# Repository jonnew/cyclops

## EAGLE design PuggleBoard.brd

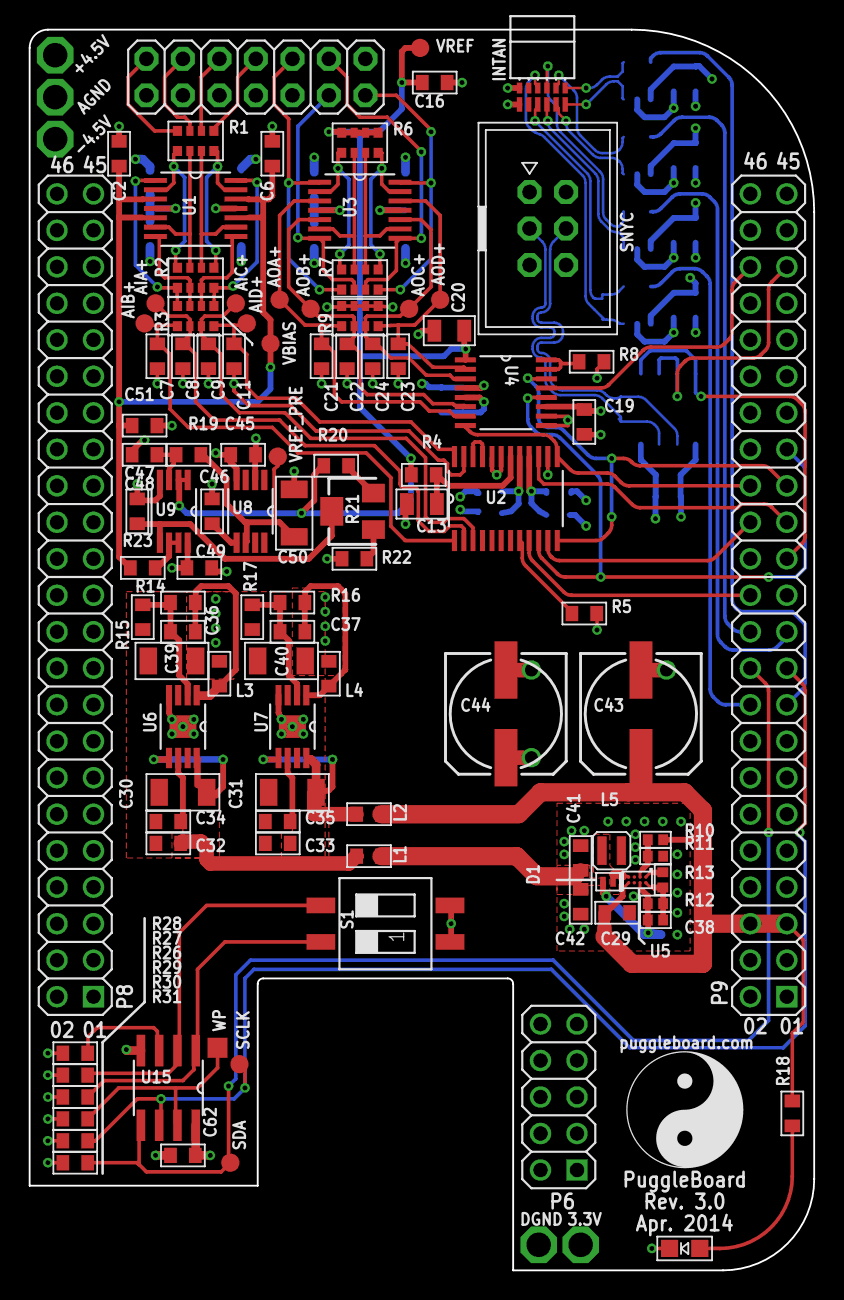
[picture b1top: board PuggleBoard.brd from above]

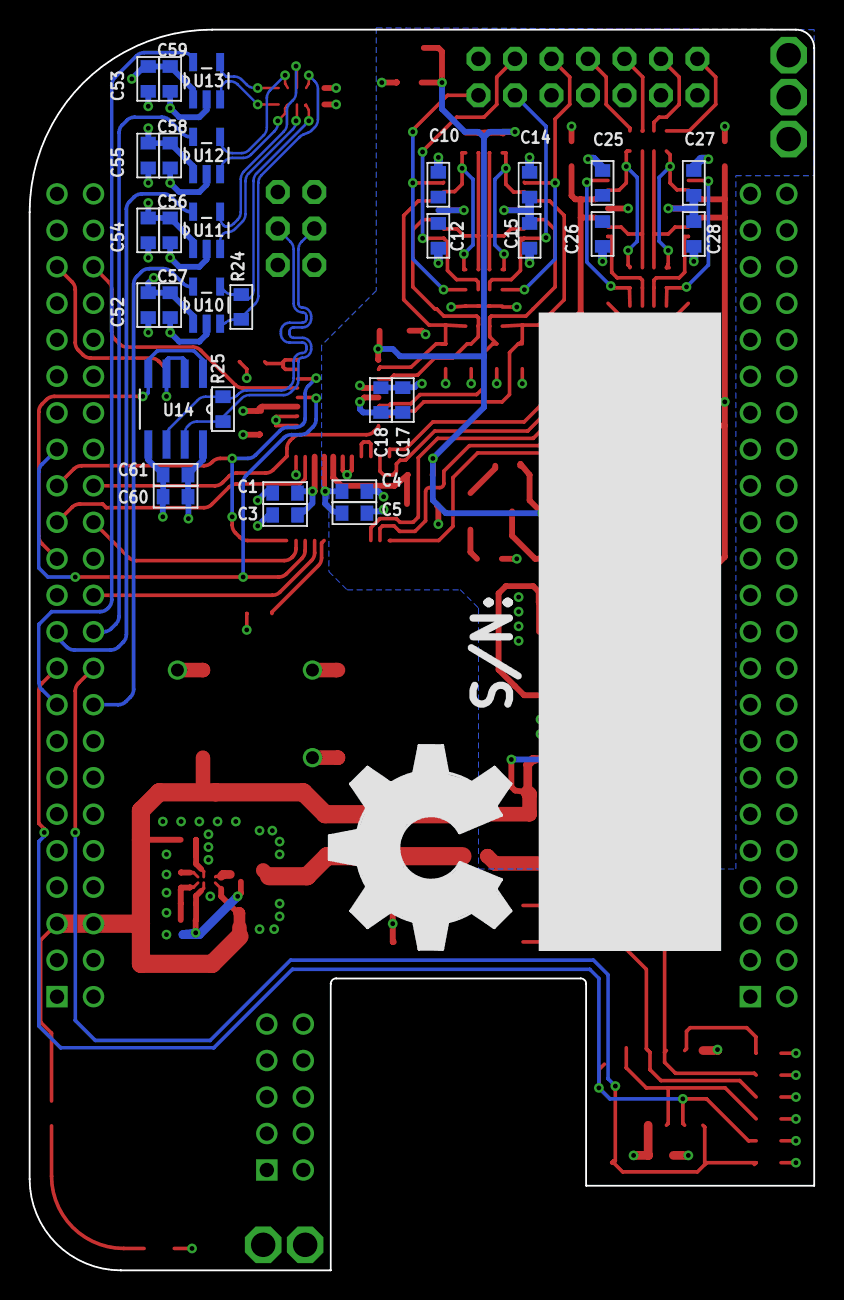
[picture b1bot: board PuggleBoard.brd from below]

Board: 4 copper layers, 54.6 x 86.4 mm, 141 parts (32 on the bottom side), 89 nets.

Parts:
3.3V: TPPAD1-17; P1-17
+4.5V: TPPAD1-17; P1-17
-4.5V: TPPAD1-17; P1-17
AGND: TPPAD1-17; P1-17
AIA+: TPB1,27; B1,27
AIB+: TPB1,27; B1,27
AIC+: TPB1,27; B1,27
AID+: TPB1,27; B1,27
AOA+: TPB1,27; B1,27
AOB+: TPB1,27; B1,27
AOC+: TPB1,27; B1,27
AOD+: TPB1,27; B1,27
A_I/O: PINHD-2X7; 2X07
BB1: BEAGLEBONE_OUTLINEPUGGLEBOARD; PUGGLEBOARD_SHIELD
C1, C4, C17: 4.7uF; 0603
C2, C3, C5, C6, C12, C15, C16, C18, C19, C26, C28, C47, C48, C49, C51, C52, C53, C54, C55, C60, C62: 0.1uF; 0603
C7, C8, C9, C11: 68nF; 0603
C10, C14, C25, C27, C45, C46: 1uF; 0603
C13: 22uF; 0805
C20: 10uF; 0805
C21, C22, C23, C24: 0603
C29: 10uF; 0603
C30, C31, C39, C40: 10uF; 1206
C32, C33, C56, C57, C58, C59, C61: 1nF; 0603
C34, C35, C36, C37: 10nF; 0603
C38: 10pF; 0402
C41, C42: 22uF; 0603
C43, C44: 47uF; 153CLV-0807
C50: 4.7uF; 1206
D1: PMEG3005EL; SOD882
DGND: TPPAD1-17; P1-17
INTAN: RHD2000-CABLE-DAQ-SIDE; OMNETICS_PZN-12-AA
L1, L2, L3, L4: MPZ1608; 0603
L5: 6.8uH; VLS2012E
PWR: LEDGREEN_0805; CHIP-LED0805
R1, R6, R7: 2k; RX4_0612
R2: 1k; RX4_0612
R3: 100; RX4_0612
R4: 10; 0603
R5, R8, R19, R23, R29: 10k; 0603
R9: RX4_0612
R10, R11: 20k; 0402
R12: 180k; 0402
R13: 39k; 0402
R14, R16: 13.7k; 0603
R15, R17, R26, R27, R28: 4.7k; 0603
R18: 1k; 0603
R20, R30, R31: 5.6k; 0603
R21: 2k; SM-42/43W
R22: 2k; 0603
R24: 100; 0603
R25: 150; 0603
S1: ADDRESS; SMS-002
SCLK: TPB1,27; B1,27
SDA: TPB1,27; B1,27
SNYC: PINHD-2X3_IDC; 2X03_IDC
U1: LMP7704; SOP65P640X120-14N-MOD
U2: ADS8331; SOP65P640X120-24N
U3: OPA4209; SOP65P640X120-14N-MOD
U4: AD5686; MO-153-AB
U5: LMR70503; 8BGA
U6: 3001; SOP65P490X110-9N
U7: 4901; SOP65P490X110-9N
U8: 5040; SOP65P490X110-8N
U9: 8032; SOP65P490X110-8N
U10: SN65LVDS2; SOT95P280X145-5N
U11, U12, U13: SN65LVDS1; SOT95P280X145-5N
U14: SN65MLVD201; SOIC127P600X175-8N
U15: 24C; SO-08
U$1: PB-LOGO-NOSITE
U$2: OSHW_FILLX500_NOTEXT
VBIAS: TPB1,27; B1,27
VREF: TPB1,27; B1,27
VREF_PRE: TPB1,27; B1,27
WP: TPTP14SQ; TP14SQ

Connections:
+4.5V: +4.5V.TP, C4.2, C5.2, C14.1, C15.1, C17.1, C18.1, C27.1, C28.1, C40.1, C45.2, C49.1, L4.2, U1.4, U2.17, U3.4, U4.5, U8.2, U9.8
+4.5V_PRE: C37.1, L4.1, R16.1, U7.1
-4.5V: -4.5V.TP, C10.1, C12.1, C25.1, C26.1, C39.1, L3.2, U1.11, U3.11
-4.5V_PRE: C36.1, L3.1, R14.1, U6.1
ADC_-IN_A: R1.P1, R2.P2, U1.2
ADC_-IN_B: R1.P3, R2.P4, U1.6
ADC_-IN_C: R1.P5, R2.P6, U1.9
ADC_-IN_D: R1.P7, R2.P8, U1.13
ADC_A: A_I/O.2, R1.P2
ADC_A+: R2.P1, R3.P2, U1.1
ADC_B: A_I/O.4, R1.P4
ADC_B+: R2.P3, R3.P4, U1.7
ADC_C: A_I/O.6, R1.P6
ADC_C+: R2.P5, R3.P6, U1.8
ADC_D: A_I/O.8, R1.P8
ADC_D+: R2.P7, R3.P8, U1.14
AGND1: C37.2, R16.2, R17.1, U7.2
AGND2: C36.2, R14.2, R15.1, U6.2
CS1_N: INTAN.T1, U13.3
CS1_P: INTAN.B1, U13.4
DAC_+IN_A: AOA+.TP, C21.1, R9.P8, U3.3, U4.7
DAC_+IN_B: AOB+.TP, C22.1, R9.P6, U3.5, U4.6
DAC_+IN_C: AOC+.TP, C24.1, R9.P4, U3.10, U4.3
DAC_+IN_D: AOD+.TP, C23.1, R9.P2, U3.12, U4.2
DAC_-IN_A: R6.P1, R7.P2, U3.2
DAC_-IN_B: R6.P3, R7.P4, U3.6
DAC_-IN_C: R6.P5, R7.P6, U3.9
DAC_-IN_D: R6.P7, R7.P8, U3.13
DAC_A: A_I/O.10, R7.P1, U3.1
DAC_B: A_I/O.11, R7.P3, U3.7
DAC_C: A_I/O.12, R7.P5, U3.8
DAC_D: A_I/O.13, R7.P7, U3.14
GND: AGND.TP, A_I/O.1, A_I/O.3, A_I/O.5, A_I/O.7, A_I/O.9, A_I/O.14, BB1.1, BB1.2, BB1.47, BB1.48, BB1.89, BB1.90, BB1.91, BB1.92, C1.2, C2.2, C3.2, C4.1, C5.1, C6.2, C7.1, C8.1, C9.1, C10.2, C11.1, C12.2, C13.1, C14.2, C15.2, C16.2, C17.2, C18.2, C19.2, C20.2, C21.2, C22.2, C23.2, C24.2, C25.2, C26.2, C27.2, C28.2, C29.2, C30.2, C31.2, C32.2, C33.2, C34.2, C35.2, C39.2, C40.2, C41.1, C42.1, C43.-, C44.-, C45.1, C46.1, C47.2, C48.2, C49.2, C50.2, C51.2, C52.2, C53.2, C54.2, C55.2, C56.2, C57.2, C58.2, C59.2, C60.2, C61.2, C62.2, DGND.TP, INTAN.T6, L5.2, PWR.C, R9.P1, R9.P3, R9.P5, R9.P7, R11.2, R15.2, R17.2, R22.2, S1.1, S1.2, SNYC.1, SNYC.2, SNYC.5, SNYC.6, U2.14, U2.19, U2.20, U2.23, U4.4, U4.9, U4.10, U5.C1, U5.C2, U6.4, U6.9, U7.4, U7.9, U8.4, U9.4, U10.2, U11.2, U12.2, U13.2, U14.5, U15.4
I2C2_SCL: BB1.65, R30.1, SCLK.TP, U15.6
I2C2_SDA: BB1.66, R31.1, SDA.TP, U15.5
MASTER/SLAVE: BB1.87, U14.2, U14.3
MISO1_N: INTAN.T4, R24.2, U10.4
MISO1_P: INTAN.B4, R24.1, U10.3
MOSI_N: INTAN.T3, U11.3
MOSI_P: INTAN.B3, U11.4
unnamed: C35.1, U7.6
unnamed: C34.1, U6.6
unnamed: U2.21, U2.22
unnamed: C48.1, R21.2, U9.5
unnamed: R10.2, R11.1, U5.B1
unnamed: R21.1, R22.1
unnamed: R23.2, U9.6, U9.7
unnamed: R20.2, R21.3
unnamed: R26.1, S1.4, U15.1
unnamed: C13.2, R4.1, U2.18
unnamed: C38.2, R12.2, R13.1, U5.A2
unnamed: R27.1, S1.3, U15.2
unnamed: R28.1, U15.3
unnamed: PWR.A, R18.1
unnamed: R29.1, U15.7, WP.TP
unnamed: R13.2, U5.A1
unnamed: C47.1, R19.1, U9.3
unnamed: C46.2, U8.5
unnamed: AIA+.TP, C7.2, R3.P1, U2.1
unnamed: AIB+.TP, C8.2, R3.P3, U2.2
unnamed: AIC+.TP, C9.2, R3.P5, U2.3
unnamed: AID+.TP, C11.2, R3.P7, U2.24
SCLK_N: INTAN.T2, U12.3
SCLK_P: INTAN.B2, U12.4
SPI0: BB1.74, U2.11
SPI1: BB1.88, U4.13
SPI2: BB1.77, U2.10, U4.12
SPI3: BB1.75, U2.12, U4.14
SPI4: BB1.76, U2.13, U4.8
SPI5: BB1.73, U2.15
SPI6: BB1.70, U2.9
SPI7: BB1.63, U13.5
SPI8: BB1.68, U12.5
SPI9: BB1.67, U11.5
SPI10: BB1.64, U10.5
SW: D1.C, L5.1, U5.D1
SYNC: BB1.71, U14.1, U14.4
SYNC_N: R25.2, SNYC.3, U14.7
SYNC_P: R25.1, SNYC.4, U14.6
VBIAS: C2.1, C6.1, C51.1, R23.1, U1.3, U1.5, U1.10, U1.12, VBIAS.TP
VDD_5V: BB1.51, BB1.52, C29.1, C43.+, L2.1, R10.1, R18.2, U5.D2
VDD_POST_LC: C31.1, C33.1, L2.2, U7.5, U7.8
VDRIVE: 3.3V.TP, BB1.49, BB1.50, C1.1, C3.1, C19.1, C44.+, C52.1, C53.1, C54.1, C55.1, C56.1, C57.1, C58.1, C59.1, C60.1, C61.1, C62.1, INTAN.B6, R5.2, R8.2, R26.2, R27.2, R28.2, R29.2, R30.2, R31.2, U2.16, U4.11, U10.1, U11.1, U12.1, U13.1, U14.8, U15.8
VOUT-: C38.1, C41.2, C42.2, D1.A, L1.1, R12.1, U5.B2
VREF: C16.1, C20.1, R4.2, R6.P2, R6.P4, R6.P6, R6.P8, R20.1, U4.1, U9.1, U9.2, VREF.TP
VREF_PRE: C50.1, R19.2, U8.6, VREF_PRE.TP
VSS_POST_LC: C30.1, C32.1, L1.2, U6.5, U6.8
~ADCRST: R5.1, U2.8
~DACRST: R8.1, U4.15, U4.16

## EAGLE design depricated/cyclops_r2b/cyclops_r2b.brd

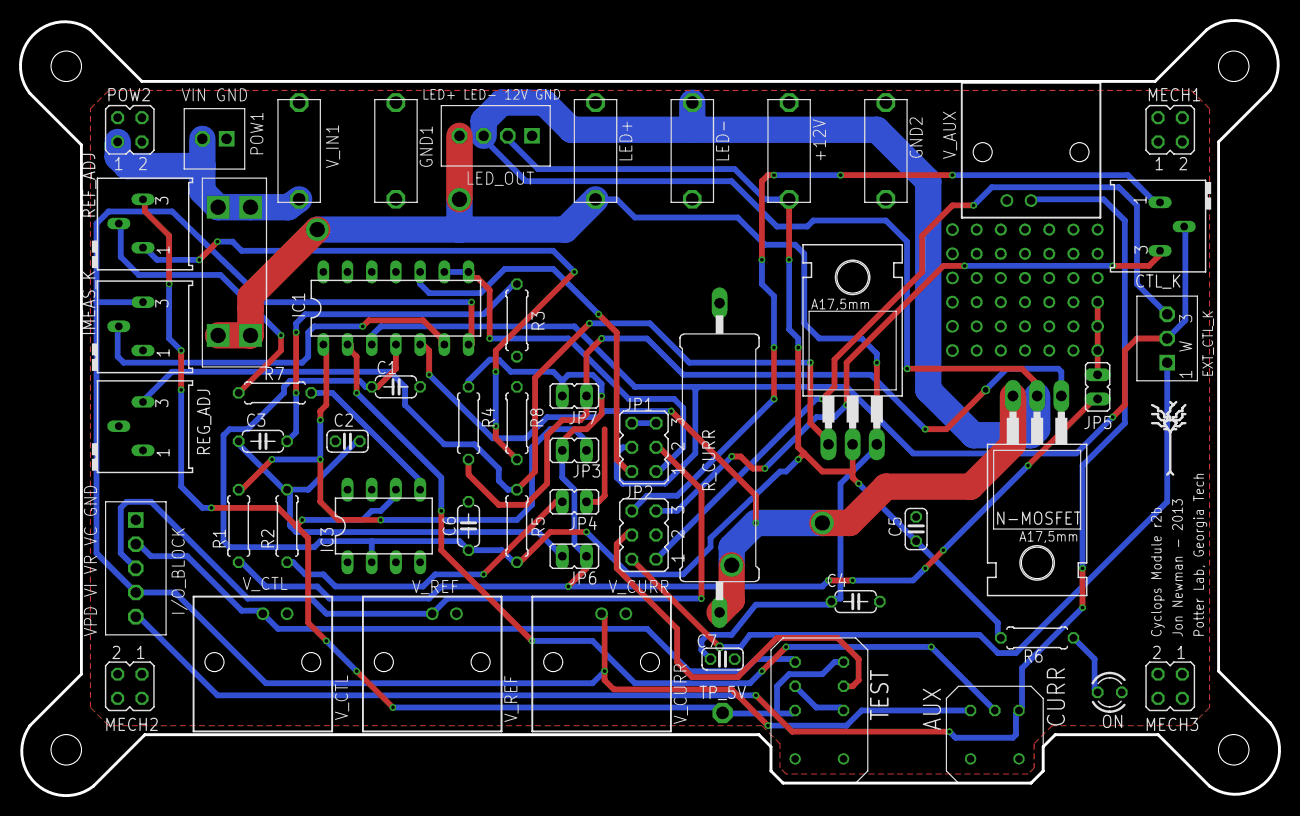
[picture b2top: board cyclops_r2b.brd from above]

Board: 2 copper layers, 132.2 x 81.4 mm, 55 parts (1 on the bottom side), 34 nets.

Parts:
+12V: BANANA_TO_BOARD
C1, C3, C4, C6: 0.1uF; C050-024X044
C2, C5: 1.0uF; C025-024X044
C7: 10uF; C025-024X044
CTL_K: 10k; RJ6S
CURR/OPT: A_TOGGLE_SPST
EXT_CTL_K: SCREW3
GND1, GND2: BANANA_TO_BOARD
I/O_BLOCK: SCREW5
IC1: LM324N; DIL14
IC2: 317; TO220BH
IC3: REF02; DIL08-OVAL
IMEAS_K: 10k; RJ6S
JP1, JP2: JP3Q
JP3, JP4, JP5, JP6, JP7: JP1
LED+: BANANA_TO_BOARD
LED-: BANANA_TO_BOARD
LED_OUT: SCREW4
MECH1, MECH2, MECH3: JP2Q
N-MOSFET: TO220BH
ON: LED3MM
POW1: SCREW2
POW2: JP2Q
R1, R2, R4: 0R; 0207/7
R3: 120; 0207/7
R5: 240; 0207/7
R6: 1.5k; 0207/7
R7: 470; 0207/7
R8: 1k; 0207/7
REF_ADJ: 10k; RJ6S
REG_ADJ: 5k; RJ6S
R_CURR: 0.2; IMEAS_R
TEST: 320-938
TP_5V: P1-13
U$1: FUSE >2A; NXT-FUSE
U$2: OSHW_FILLX750_NOTEXT
V_AUX: 1-227161-0; AMP_227161
V_CTL: 1-227161-0; AMP_227161
V_CURR: 1-227161-0; AMP_227161
V_IN1: BANANA_TO_BOARD
V_REF: 1-227161-0; AMP_227161

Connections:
GND: C1.2, C2.2, C4.2, C5.2, C6.2, C7.1, GND1.P$1, GND1.P$2, GND2.P$1, GND2.P$2, I/O_BLOCK.P$1, IC1.11, IC3.4, IMEAS_K.A, JP2.3, JP4.1, LED_OUT.P$1, ON.K, POW1.P$1, POW2.4, R3.1, R8.2, REG_ADJ.S, R_CURR.1, V_AUX.2, V_CTL.2, V_CURR.2, V_REF.2
unnamed: CURR/OPT.P$2, IC1.2
unnamed: IC1.5, N-MOSFET.S, R_CURR.2
unnamed: IC1.1, JP3.2, R1.2
unnamed: CURR/OPT.P$1, I/O_BLOCK.P$4, IC1.7, IMEAS_K.E, V_CURR.1
unnamed: CURR/OPT.P$3, I/O_BLOCK.P$5, V_AUX.1
unnamed: JP2.4, TEST.P$2
unnamed: CTL_K.E, JP2.5
unnamed: CTL_K.S, EXT_CTL_K.P$2, IC1.3, JP1.4
unnamed: IC1.8, IC1.9, JP1.1
unnamed: I/O_BLOCK.P$2, TEST.P$4, V_CTL.1
unnamed: C2.1, C3.1, JP6.2, R2.2
unnamed: CTL_K.A, JP2.6
unnamed: C3.2, R3.2
unnamed: IC1.10, JP1.2
unnamed: IC1.6, IMEAS_K.S
unnamed: JP1.5, JP1.6
unnamed: I/O_BLOCK.P$3, JP1.3, V_REF.1
unnamed: IC2.G, R5.1, REG_ADJ.E
unnamed: IC3.5, R7.2
unnamed: LED-.P$1, LED-.P$2, LED_OUT.P$3, N-MOSFET.D
unnamed: R7.1, REF_ADJ.S
unnamed: TEST.P$3, TEST.P$5
unnamed: R8.1, REF_ADJ.A
unnamed: EXT_CTL_K.P$1, JP2.2
unnamed: EXT_CTL_K.P$3, JP2.1
unnamed: JP4.2, R2.1
unnamed: ON.A, R6.1
unnamed: JP3.1, JP5.2, JP6.1, JP7.2, R1.1, R4.2
unnamed: JP7.1, N-MOSFET.G, R4.1
P_12V: +12V.P$1, +12V.P$2, C1.1, C5.1, C6.1, IC1.4, IC2.D, IC3.2, LED_OUT.P$2, R5.2, R6.2
P_SUP: C4.1, C7.2, IC2.S, LED+.P$1, LED+.P$2, LED_OUT.P$4, U$1.P$4, U$1.P$53
P_SUP_BEFORE: POW1.P$2, POW2.1, U$1.P$1, U$1.P$2, V_IN1.P$1, V_IN1.P$2
REF_5V: IC3.6, REF_ADJ.E, TEST.P$1, TEST.P$6, TP_5V.TP

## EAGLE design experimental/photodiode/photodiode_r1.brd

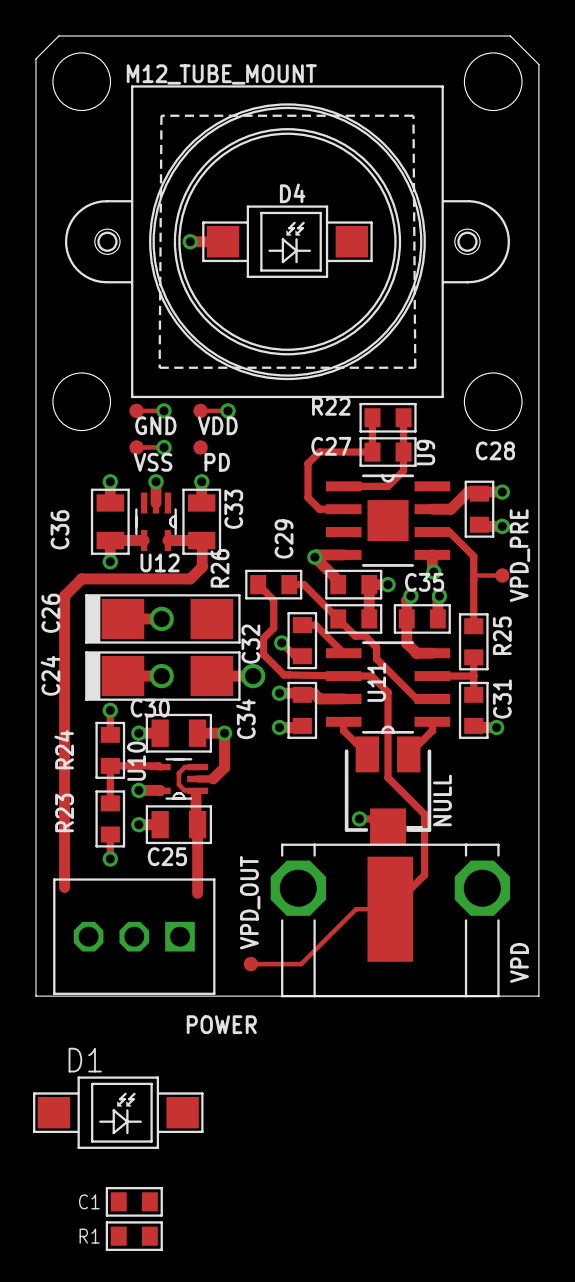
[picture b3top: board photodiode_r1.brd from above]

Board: 4 copper layers, 27.9 x 53.3 mm, 37 parts (0 on the bottom side), 17 nets.

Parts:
C1, C28, C29, C34, C35: .1uF; 0603
C24, C26: 10uF; 6032M-POL
C25, C30, C33, C36: 1uF; 0805
C27: 15pF; 0603
C31: 56pF; 0603
C32: 10pF; 0603
D1, D4: VBPW34S
GND: TPTP08R; TP08R
M12_TUBE_MOUNT: PT-LH001
NULL: 20k; SM-42/43A
PD: TPTP08R; TP08R
POWER: S2B-PH-K-S; SCREW3
R1, R23: 20k; 0603
R22: 1.24k; 0603
R24: 4.3k; 0603
R25: 140; 0603
R26: 237; 0603
R27: 79; 0603
U9: ADA4899; SOIC127P600X175-9N
U10: MIC5225; SOT65P210X110-5N
U11: AD829; SOIC127P600X175-8N
U12: MIC5270; SOT65P210X110-5N
VDD: TPTP08R; TP08R
VPD: 361V509E
VPD_OUT: TPTP08R; TP08R
VPD_PRE: TPTP08R; TP08R
VSS: TPTP08R; TP08R

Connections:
+7V: C24.+, C28.1, C30.1, C34.1, R23.1, U9.7, U10.5, U11.7, VDD.TP
+12V: C25.1, POWER.P$1, U10.1, U10.3
-5V: C26.-, C29.1, C35.1, C36.1, D1.A, D4.A, NULL.2, U9.4, U9.5, U11.4, U12.4, VSS.TP
-6V: C33.1, POWER.P$3, U12.5
AGND: C1.2, R1.1
GND: C24.-, C25.2, C26.+, C28.2, C29.2, C30.2, C31.2, C32.2, C33.2, C34.2, C35.2, C36.2, GND.TP, POWER.P$2, R24.2, R27.1, U10.2, U12.2, VPD.2, VPD.3
unnamed: C1.1, D1.C, R1.2, U9.3
unnamed: C27.1, R22.2, U9.1
unnamed: C27.2, D4.C, PD.TP, R22.1, U9.2
unnamed: NULL.3, U11.1
unnamed: R25.1, U9.6, VPD_PRE.TP
unnamed: R23.2, R24.1, U10.4
unnamed: R26.2, R27.2, U11.2
unnamed: NULL.1, U11.8
unnamed: C32.1, U11.5
VPD: R26.1, U11.6, VPD.1, VPD_OUT.TP
VPD_PRE: C31.1, R25.2, U11.3
